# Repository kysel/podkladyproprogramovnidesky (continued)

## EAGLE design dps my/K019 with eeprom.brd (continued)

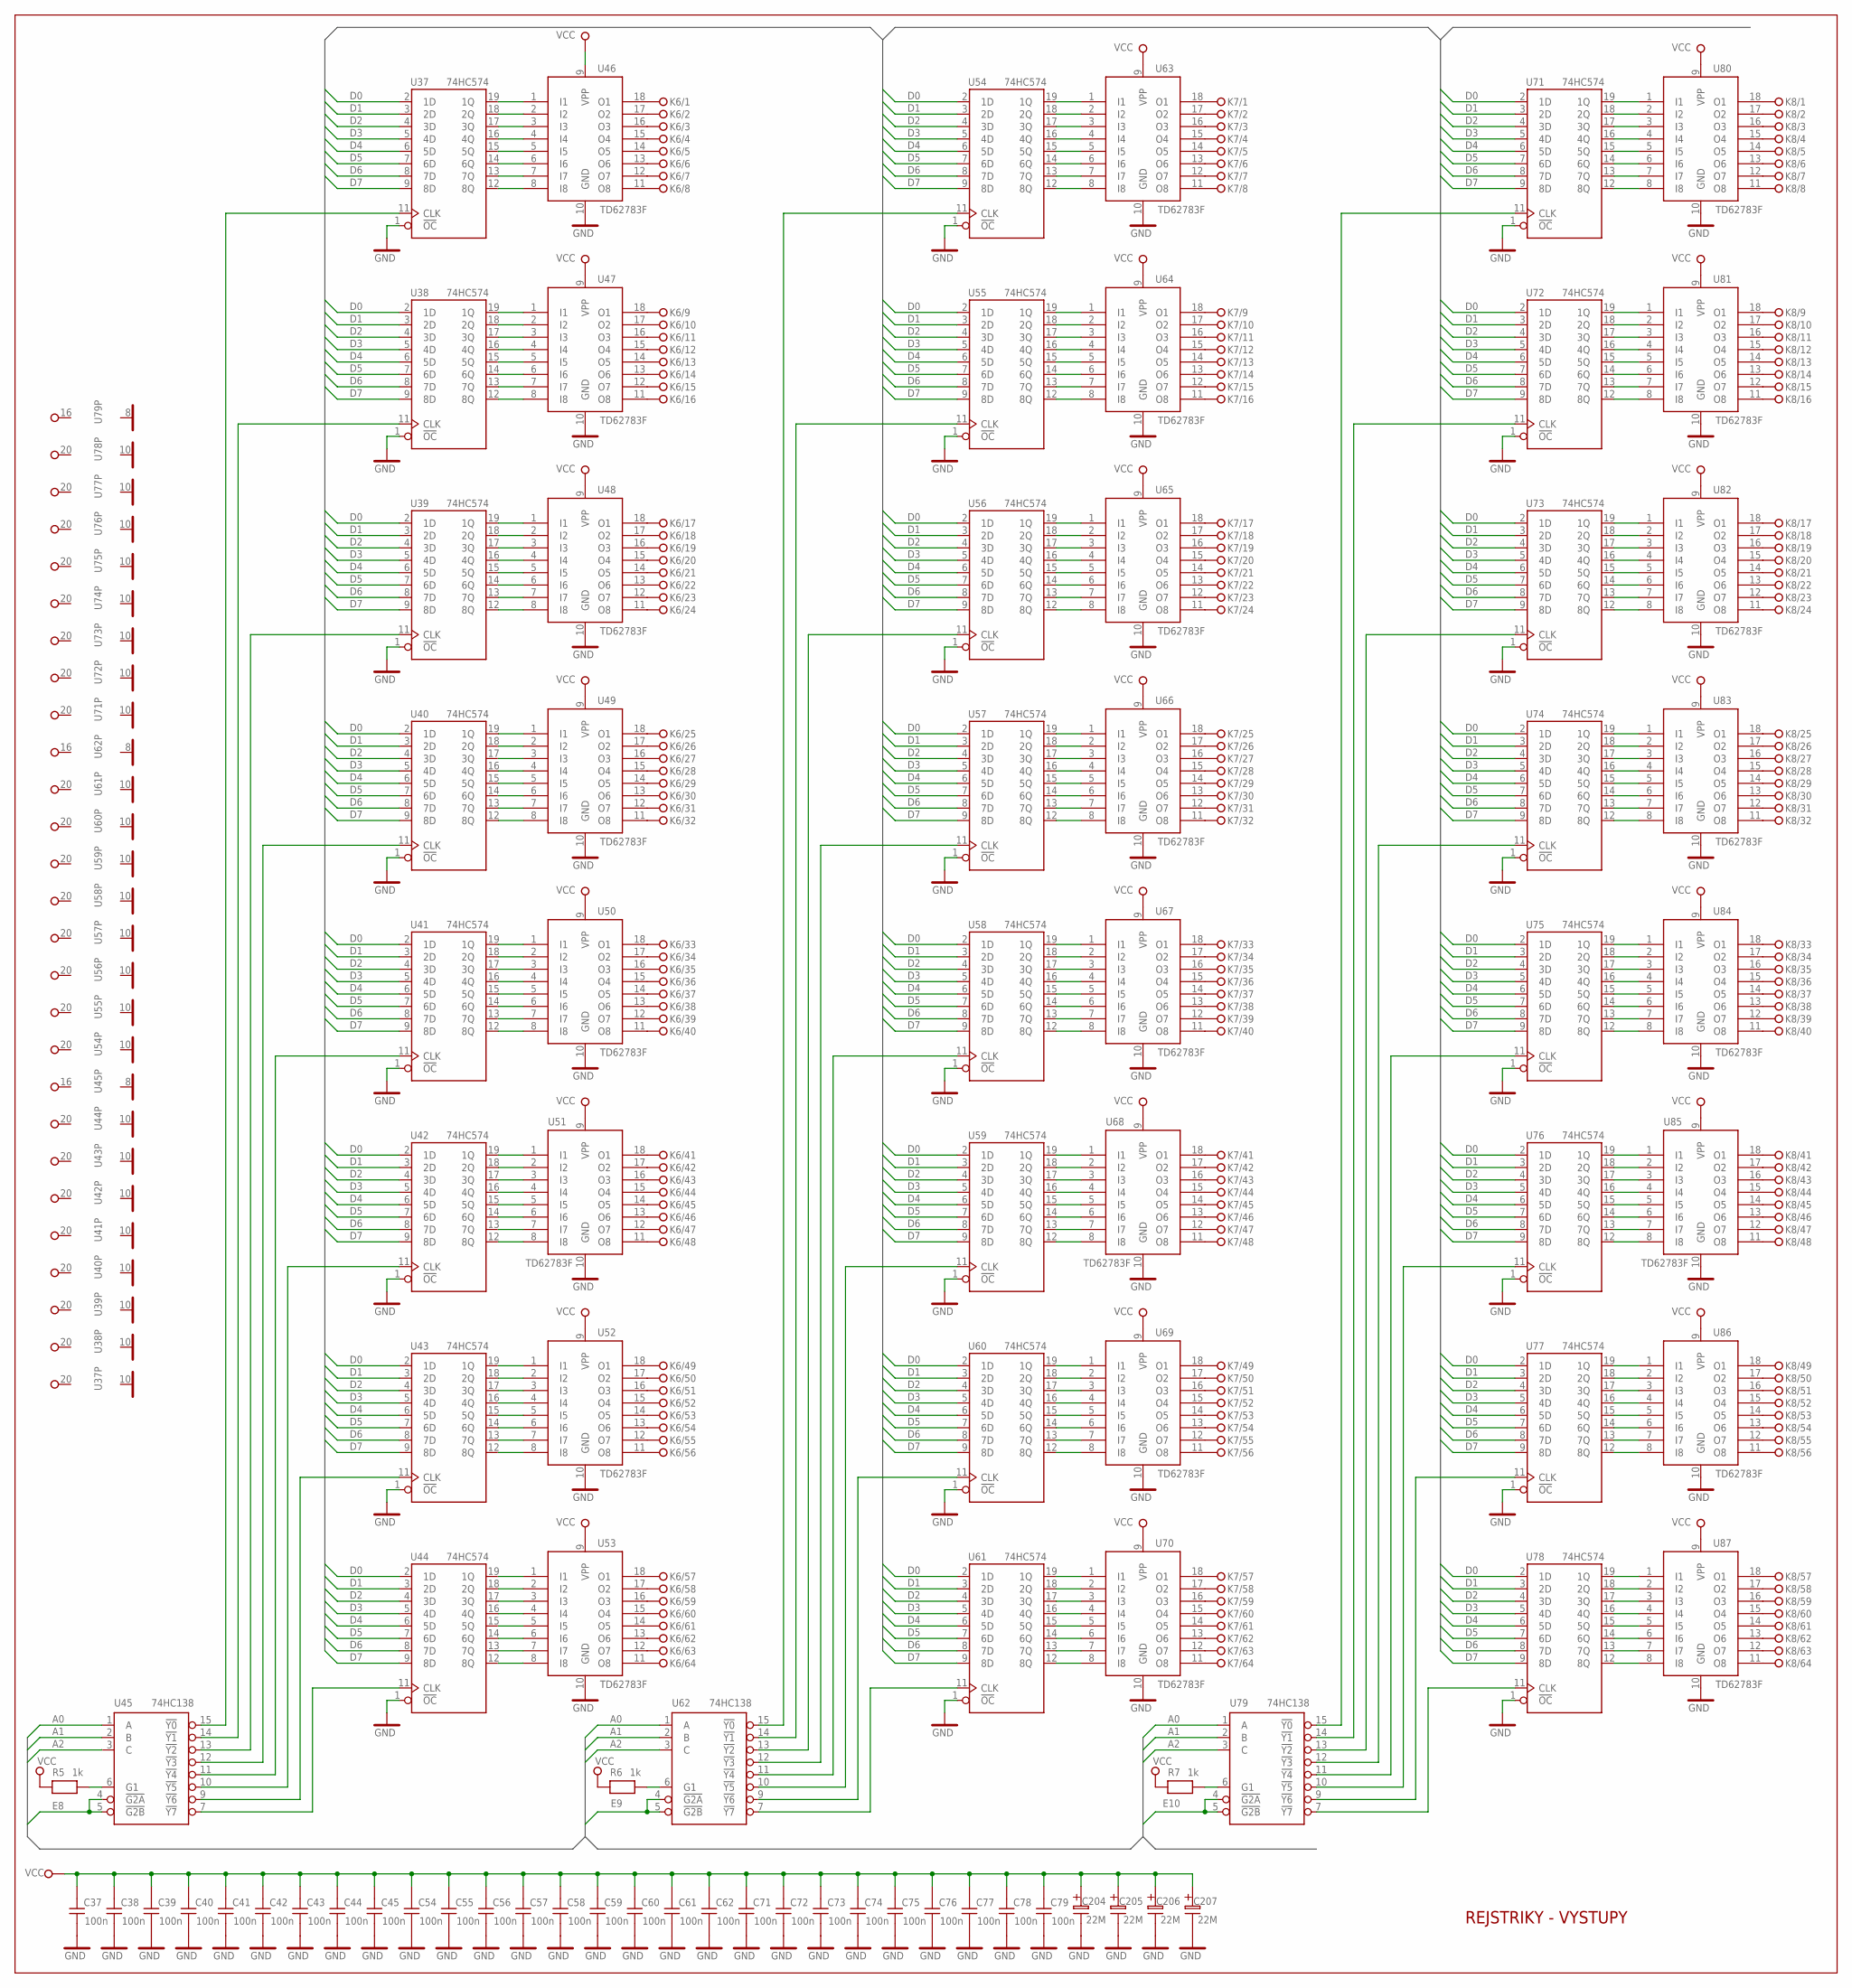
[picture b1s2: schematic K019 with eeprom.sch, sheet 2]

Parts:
C37, C38, C39, C40, C41, C42, C43, C44, C45, C54, C55, C56, C57, C58, C59, C60, C61, C62, C71, C72, C73, C74, C75, C76, C77, C78, C79: 100n; C-5-2X8
C204, C205, C206, C207: 22M; EC-2/5
K6, K7, K8: KON64
R5, R6, R7: 1k; R-7,5
U37, U38, U39, U40, U41, U42, U43, U44, U54, U55, U56, U57, U58, U59, U60, U61, U71, U72, U73, U74, U75, U76, U77, U78: 74HC574; DIL20
U45, U62, U79: 74HC138; DIL16
U46, U47, U48, U49, U50, U51, U52, U53, U63, U64, U65, U66, U67, U68, U69, U70, U80, U81, U82, U83, U84, U85, U86, U87: TD62783F; DIL18

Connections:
A0: U45.1 (A), U62.1 (A), U79.1 (A); also elsewhere on the board
A1: U45.2 (B), U62.2 (B), U79.2 (B); also elsewhere on the board
A2: U45.3 (C), U62.3 (C), U79.3 (C); also elsewhere on the board
D0: U37.2 (1D), U38.2 (1D), U39.2 (1D), U40.2 (1D), U41.2 (1D), U42.2 (1D), U43.2 (1D), U44.2 (1D), U54.2 (1D), U55.2 (1D), U56.2 (1D), U57.2 (1D), U58.2 (1D), U59.2 (1D), U60.2 (1D), U61.2 (1D), U71.2 (1D), U72.2 (1D), U73.2 (1D), U74.2 (1D), U75.2 (1D), U76.2 (1D), U77.2 (1D), U78.2 (1D); also elsewhere on the board
D1: U37.3 (2D), U38.3 (2D), U39.3 (2D), U40.3 (2D), U41.3 (2D), U42.3 (2D), U43.3 (2D), U44.3 (2D), U54.3 (2D), U55.3 (2D), U56.3 (2D), U57.3 (2D), U58.3 (2D), U59.3 (2D), U60.3 (2D), U61.3 (2D), U71.3 (2D), U72.3 (2D), U73.3 (2D), U74.3 (2D), U75.3 (2D), U76.3 (2D), U77.3 (2D), U78.3 (2D); also elsewhere on the board
D2: U37.4 (3D), U38.4 (3D), U39.4 (3D), U40.4 (3D), U41.4 (3D), U42.4 (3D), U43.4 (3D), U44.4 (3D), U54.4 (3D), U55.4 (3D), U56.4 (3D), U57.4 (3D), U58.4 (3D), U59.4 (3D), U60.4 (3D), U61.4 (3D), U71.4 (3D), U72.4 (3D), U73.4 (3D), U74.4 (3D), U75.4 (3D), U76.4 (3D), U77.4 (3D), U78.4 (3D); also elsewhere on the board
D3: U37.5 (4D), U38.5 (4D), U39.5 (4D), U40.5 (4D), U41.5 (4D), U42.5 (4D), U43.5 (4D), U44.5 (4D), U54.5 (4D), U55.5 (4D), U56.5 (4D), U57.5 (4D), U58.5 (4D), U59.5 (4D), U60.5 (4D), U61.5 (4D), U71.5 (4D), U72.5 (4D), U73.5 (4D), U74.5 (4D), U75.5 (4D), U76.5 (4D), U77.5 (4D), U78.5 (4D); also elsewhere on the board
D4: U37.6 (5D), U38.6 (5D), U39.6 (5D), U40.6 (5D), U41.6 (5D), U42.6 (5D), U43.6 (5D), U44.6 (5D), U54.6 (5D), U55.6 (5D), U56.6 (5D), U57.6 (5D), U58.6 (5D), U59.6 (5D), U60.6 (5D), U61.6 (5D), U71.6 (5D), U72.6 (5D), U73.6 (5D), U74.6 (5D), U75.6 (5D), U76.6 (5D), U77.6 (5D), U78.6 (5D); also elsewhere on the board
D5: U37.7 (6D), U38.7 (6D), U39.7 (6D), U40.7 (6D), U41.7 (6D), U42.7 (6D), U43.7 (6D), U44.7 (6D), U54.7 (6D), U55.7 (6D), U56.7 (6D), U57.7 (6D), U58.7 (6D), U59.7 (6D), U60.7 (6D), U61.7 (6D), U71.7 (6D), U72.7 (6D), U73.7 (6D), U74.7 (6D), U75.7 (6D), U76.7 (6D), U77.7 (6D), U78.7 (6D); also elsewhere on the board
D6: U37.8 (7D), U38.8 (7D), U39.8 (7D), U40.8 (7D), U41.8 (7D), U42.8 (7D), U43.8 (7D), U44.8 (7D), U54.8 (7D), U55.8 (7D), U56.8 (7D), U57.8 (7D), U58.8 (7D), U59.8 (7D), U60.8 (7D), U61.8 (7D), U71.8 (7D), U72.8 (7D), U73.8 (7D), U74.8 (7D), U75.8 (7D), U76.8 (7D), U77.8 (7D), U78.8 (7D); also elsewhere on the board
D7: U37.9 (8D), U38.9 (8D), U39.9 (8D), U40.9 (8D), U41.9 (8D), U42.9 (8D), U43.9 (8D), U44.9 (8D), U54.9 (8D), U55.9 (8D), U56.9 (8D), U57.9 (8D), U58.9 (8D), U59.9 (8D), U60.9 (8D), U61.9 (8D), U71.9 (8D), U72.9 (8D), U73.9 (8D), U74.9 (8D), U75.9 (8D), U76.9 (8D), U77.9 (8D), U78.9 (8D); also elsewhere on the board
E8: U45.4 (!G2A), U45.5 (!G2B); also elsewhere on the board
E9: U62.4 (!G2A), U62.5 (!G2B); also elsewhere on the board
E10: U79.4 (!G2A), U79.5 (!G2B); also elsewhere on the board
GND: C37.1, C38.1, C39.1, C40.1, C41.1, C42.1, C43.1, C44.1, C45.1, C54.1, C55.1, C56.1, C57.1, C58.1, C59.1, C60.1, C61.1, C62.1, C71.1, C72.1, C73.1, C74.1, C75.1, C76.1, C77.1, C78.1, C79.1, C204.1, C205.1, C206.1, C207.1, U37.1 (!OC), U37.10 (GND), U38.1 (!OC), U38.10 (GND), U39.1 (!OC), U39.10 (GND), U40.1 (!OC), U40.10 (GND), U41.1 (!OC), U41.10 (GND), U42.1 (!OC), U42.10 (GND), U43.1 (!OC), U43.10 (GND), U44.1 (!OC), U44.10 (GND), U45.8 (GND), U46.10 (GND), U47.10 (GND), U48.10 (GND), U49.10 (GND), U50.10 (GND), U51.10 (GND), U52.10 (GND), U53.10 (GND), U54.1 (!OC), U54.10 (GND), U55.1 (!OC), U55.10 (GND), U56.1 (!OC), U56.10 (GND), U57.1 (!OC), U57.10 (GND), U58.1 (!OC), U58.10 (GND), U59.1 (!OC), U59.10 (GND), U60.1 (!OC), U60.10 (GND), U61.1 (!OC), U61.10 (GND), U62.8 (GND), U63.10 (GND), U64.10 (GND), U65.10 (GND), U66.10 (GND), U67.10 (GND), U68.10 (GND), U69.10 (GND), U70.10 (GND), U71.1 (!OC), U71.10 (GND), U72.1 (!OC), U72.10 (GND), U73.1 (!OC), U73.10 (GND), U74.1 (!OC), U74.10 (GND), U75.1 (!OC), U75.10 (GND), U76.1 (!OC), U76.10 (GND), U77.1 (!OC), U77.10 (GND), U78.1 (!OC), U78.10 (GND), U79.8 (GND), U80.10 (GND), U81.10 (GND), U82.10 (GND), U83.10 (GND), U84.10 (GND), U85.10 (GND), U86.10 (GND), U87.10 (GND); also elsewhere on the board
unnamed: K6.1, U46.18 (O1)
unnamed: K6.2, U46.17 (O2)
unnamed: K6.3, U46.16 (O3)
unnamed: K6.4, U46.15 (O4)
unnamed: K6.5, U46.14 (O5)
unnamed: K6.6, U46.13 (O6)
unnamed: K6.7, U46.12 (O7)
unnamed: K6.8, U46.11 (O8)
unnamed: K6.9, U47.18 (O1)
unnamed: K6.10, U47.17 (O2)
unnamed: K6.11, U47.16 (O3)
unnamed: K6.12, U47.15 (O4)
unnamed: K6.13, U47.14 (O5)
unnamed: K6.14, U47.13 (O6)
unnamed: K6.15, U47.12 (O7)
unnamed: K6.16, U47.11 (O8)
unnamed: K6.17, U48.18 (O1)
unnamed: K6.18, U48.17 (O2)
unnamed: K6.19, U48.16 (O3)
unnamed: K6.20, U48.15 (O4)
unnamed: K6.21, U48.14 (O5)
unnamed: K6.22, U48.13 (O6)
unnamed: K6.23, U48.12 (O7)
unnamed: K6.24, U48.11 (O8)
unnamed: K6.25, U49.18 (O1)
unnamed: K6.26, U49.17 (O2)
unnamed: K6.27, U49.16 (O3)
unnamed: K6.28, U49.15 (O4)
unnamed: K6.29, U49.14 (O5)
unnamed: K6.30, U49.13 (O6)
unnamed: K6.31, U49.12 (O7)
unnamed: K6.32, U49.11 (O8)
unnamed: K6.33, U50.18 (O1)
unnamed: K6.34, U50.17 (O2)
unnamed: K6.35, U50.16 (O3)
unnamed: K6.36, U50.15 (O4)
unnamed: K6.37, U50.14 (O5)
unnamed: K6.38, U50.13 (O6)
unnamed: K6.39, U50.12 (O7)
unnamed: K6.40, U50.11 (O8)
unnamed: K6.41, U51.18 (O1)
unnamed: K6.42, U51.17 (O2)
unnamed: K6.43, U51.16 (O3)
unnamed: K6.44, U51.15 (O4)
unnamed: K6.45, U51.14 (O5)
unnamed: K6.46, U51.13 (O6)
unnamed: K6.47, U51.12 (O7)
unnamed: K6.48, U51.11 (O8)
unnamed: K6.49, U52.18 (O1)
unnamed: K6.50, U52.17 (O2)
unnamed: K6.51, U52.16 (O3)
unnamed: K6.52, U52.15 (O4)
unnamed: K6.53, U52.14 (O5)
unnamed: K6.54, U52.13 (O6)
unnamed: K6.55, U52.12 (O7)
unnamed: K6.56, U52.11 (O8)
unnamed: K6.57, U53.18 (O1)
unnamed: K6.58, U53.17 (O2)
unnamed: K6.59, U53.16 (O3)
unnamed: K6.60, U53.15 (O4)
unnamed: K6.61, U53.14 (O5)
unnamed: K6.62, U53.13 (O6)
unnamed: K6.63, U53.12 (O7)
unnamed: K6.64, U53.11 (O8)
unnamed: U44.12 (8Q), U53.8 (I8)
unnamed: U44.13 (7Q), U53.7 (I7)
unnamed: U44.14 (6Q), U53.6 (I6)
unnamed: U44.15 (5Q), U53.5 (I5)
unnamed: U44.16 (4Q), U53.4 (I4)
unnamed: U44.17 (3Q), U53.3 (I3)
unnamed: U44.18 (2Q), U53.2 (I2)
unnamed: U44.19 (1Q), U53.1 (I1)
unnamed: U43.12 (8Q), U52.8 (I8)
unnamed: U43.13 (7Q), U52.7 (I7)
unnamed: U43.14 (6Q), U52.6 (I6)
unnamed: U43.15 (5Q), U52.5 (I5)
unnamed: U43.16 (4Q), U52.4 (I4)
unnamed: U43.17 (3Q), U52.3 (I3)
unnamed: U43.18 (2Q), U52.2 (I2)
unnamed: U43.19 (1Q), U52.1 (I1)
unnamed: U41.19 (1Q), U50.1 (I1)
unnamed: U41.18 (2Q), U50.2 (I2)
unnamed: U41.17 (3Q), U50.3 (I3)
unnamed: U41.16 (4Q), U50.4 (I4)
unnamed: U41.15 (5Q), U50.5 (I5)
unnamed: U41.14 (6Q), U50.6 (I6)
unnamed: U41.13 (7Q), U50.7 (I7)
unnamed: U41.12 (8Q), U50.8 (I8)
unnamed: U42.12 (8Q), U51.8 (I8)
unnamed: U42.13 (7Q), U51.7 (I7)
unnamed: U42.14 (6Q), U51.6 (I6)
unnamed: U42.15 (5Q), U51.5 (I5)
unnamed: U42.16 (4Q), U51.4 (I4)
unnamed: U42.17 (3Q), U51.3 (I3)
unnamed: U42.18 (2Q), U51.2 (I2)
unnamed: U40.12 (8Q), U49.8 (I8)
unnamed: U40.13 (7Q), U49.7 (I7)
unnamed: U40.14 (6Q), U49.6 (I6)
unnamed: U40.15 (5Q), U49.5 (I5)
unnamed: U40.16 (4Q), U49.4 (I4)
unnamed: U40.17 (3Q), U49.3 (I3)
unnamed: U40.18 (2Q), U49.2 (I2)
unnamed: U40.19 (1Q), U49.1 (I1)
unnamed: U38.19 (1Q), U47.1 (I1)
unnamed: U38.18 (2Q), U47.2 (I2)
unnamed: U38.17 (3Q), U47.3 (I3)
unnamed: U38.16 (4Q), U47.4 (I4)
unnamed: U38.15 (5Q), U47.5 (I5)
unnamed: U38.14 (6Q), U47.6 (I6)
unnamed: U38.13 (7Q), U47.7 (I7)
unnamed: U38.12 (8Q), U47.8 (I8)
unnamed: U39.19 (1Q), U48.1 (I1)
unnamed: U39.18 (2Q), U48.2 (I2)
unnamed: U39.17 (3Q), U48.3 (I3)
unnamed: U39.16 (4Q), U48.4 (I4)
unnamed: U39.15 (5Q), U48.5 (I5)
unnamed: U39.14 (6Q), U48.6 (I6)
unnamed: U39.13 (7Q), U48.7 (I7)
unnamed: U39.12 (8Q), U48.8 (I8)
unnamed: U37.12 (8Q), U46.8 (I8)
unnamed: U37.13 (7Q), U46.7 (I7)
unnamed: U37.14 (6Q), U46.6 (I6)
unnamed: U37.15 (5Q), U46.5 (I5)
unnamed: U37.16 (4Q), U46.4 (I4)
unnamed: U37.17 (3Q), U46.3 (I3)
unnamed: U37.18 (2Q), U46.2 (I2)
unnamed: U37.19 (1Q), U46.1 (I1)
unnamed: U42.19 (1Q), U51.1 (I1)
unnamed: U44.11 (CLK), U45.7 (!Y7)
unnamed: U43.11 (CLK), U45.9 (!Y6)
unnamed: U42.11 (CLK), U45.10 (!Y5)
unnamed: U41.11 (CLK), U45.11 (!Y4)
unnamed: U40.11 (CLK), U45.12 (!Y3)
unnamed: U39.11 (CLK), U45.13 (!Y2)
unnamed: U38.11 (CLK), U45.14 (!Y1)
unnamed: U37.11 (CLK), U45.15 (!Y0)
unnamed: R5.2, U45.6 (G1)
unnamed: K7.1, U63.18 (O1)
unnamed: K7.2, U63.17 (O2)
unnamed: K7.3, U63.16 (O3)
unnamed: K7.4, U63.15 (O4)
unnamed: K7.5, U63.14 (O5)
unnamed: K7.6, U63.13 (O6)
unnamed: K7.7, U63.12 (O7)
unnamed: K7.8, U63.11 (O8)
unnamed: K7.9, U64.18 (O1)
unnamed: K7.10, U64.17 (O2)
unnamed: K7.11, U64.16 (O3)
unnamed: K7.12, U64.15 (O4)
unnamed: K7.13, U64.14 (O5)
unnamed: K7.14, U64.13 (O6)
unnamed: K7.15, U64.12 (O7)
unnamed: K7.16, U64.11 (O8)
unnamed: K7.25, U66.18 (O1)
unnamed: K7.26, U66.17 (O2)
unnamed: K7.27, U66.16 (O3)
unnamed: K7.28, U66.15 (O4)
unnamed: K7.29, U66.14 (O5)
unnamed: K7.30, U66.13 (O6)
unnamed: K7.31, U66.12 (O7)
unnamed: K7.32, U66.11 (O8)
unnamed: K7.33, U67.18 (O1)
unnamed: K7.34, U67.17 (O2)
unnamed: K7.35, U67.16 (O3)
unnamed: K7.36, U67.15 (O4)
unnamed: K7.37, U67.14 (O5)
unnamed: K7.38, U67.13 (O6)
unnamed: K7.39, U67.12 (O7)
unnamed: K7.40, U67.11 (O8)
unnamed: K7.41, U68.18 (O1)
unnamed: K7.42, U68.17 (O2)
unnamed: K7.43, U68.16 (O3)
unnamed: K7.44, U68.15 (O4)
unnamed: K7.45, U68.14 (O5)
unnamed: K7.46, U68.13 (O6)
unnamed: K7.47, U68.12 (O7)
unnamed: K7.48, U68.11 (O8)
unnamed: K7.49, U69.18 (O1)
unnamed: K7.50, U69.17 (O2)
unnamed: K7.51, U69.16 (O3)
unnamed: K7.52, U69.15 (O4)
unnamed: K7.53, U69.14 (O5)
unnamed: K7.54, U69.13 (O6)
unnamed: K7.55, U69.12 (O7)
unnamed: K7.56, U69.11 (O8)
unnamed: K7.57, U70.18 (O1)
unnamed: K7.58, U70.17 (O2)
unnamed: K7.59, U70.16 (O3)
unnamed: K7.60, U70.15 (O4)
unnamed: K7.61, U70.14 (O5)
unnamed: K7.62, U70.13 (O6)
unnamed: K7.63, U70.12 (O7)
unnamed: K7.64, U70.11 (O8)
unnamed: U61.12 (8Q), U70.8 (I8)
unnamed: U61.13 (7Q), U70.7 (I7)
unnamed: U61.14 (6Q), U70.6 (I6)
unnamed: U61.15 (5Q), U70.5 (I5)
unnamed: U61.16 (4Q), U70.4 (I4)
unnamed: U61.17 (3Q), U70.3 (I3)
unnamed: U61.18 (2Q), U70.2 (I2)
unnamed: U61.19 (1Q), U70.1 (I1)
unnamed: U60.12 (8Q), U69.8 (I8)
unnamed: U60.13 (7Q), U69.7 (I7)
unnamed: U60.14 (6Q), U69.6 (I6)
unnamed: U60.15 (5Q), U69.5 (I5)
unnamed: U60.16 (4Q), U69.4 (I4)
unnamed: U60.17 (3Q), U69.3 (I3)
unnamed: U60.18 (2Q), U69.2 (I2)
unnamed: U60.19 (1Q), U69.1 (I1)
unnamed: U58.19 (1Q), U67.1 (I1)
unnamed: U58.18 (2Q), U67.2 (I2)
unnamed: U58.17 (3Q), U67.3 (I3)
unnamed: U58.16 (4Q), U67.4 (I4)
unnamed: U58.15 (5Q), U67.5 (I5)
unnamed: U58.14 (6Q), U67.6 (I6)
unnamed: U58.13 (7Q), U67.7 (I7)
unnamed: U58.12 (8Q), U67.8 (I8)
unnamed: U59.19 (1Q), U68.1 (I1)
unnamed: U59.18 (2Q), U68.2 (I2)
unnamed: U59.17 (3Q), U68.3 (I3)
unnamed: U59.16 (4Q), U68.4 (I4)
unnamed: U59.15 (5Q), U68.5 (I5)
unnamed: U59.14 (6Q), U68.6 (I6)
unnamed: U59.13 (7Q), U68.7 (I7)
unnamed: K7.17, U65.18 (O1)
unnamed: K7.18, U65.17 (O2)
unnamed: K7.19, U65.16 (O3)
unnamed: K7.20, U65.15 (O4)
unnamed: K7.21, U65.14 (O5)
unnamed: K7.22, U65.13 (O6)
unnamed: K7.23, U65.12 (O7)
unnamed: K7.24, U65.11 (O8)
unnamed: U57.12 (8Q), U66.8 (I8)
unnamed: U57.13 (7Q), U66.7 (I7)
unnamed: U57.14 (6Q), U66.6 (I6)
unnamed: U57.15 (5Q), U66.5 (I5)
unnamed: U57.16 (4Q), U66.4 (I4)
unnamed: U57.17 (3Q), U66.3 (I3)
unnamed: U57.18 (2Q), U66.2 (I2)
unnamed: U57.19 (1Q), U66.1 (I1)
unnamed: U55.19 (1Q), U64.1 (I1)
unnamed: U55.18 (2Q), U64.2 (I2)
unnamed: U55.17 (3Q), U64.3 (I3)
unnamed: U55.16 (4Q), U64.4 (I4)
unnamed: U55.15 (5Q), U64.5 (I5)
unnamed: U55.14 (6Q), U64.6 (I6)
unnamed: U55.13 (7Q), U64.7 (I7)
unnamed: U55.12 (8Q), U64.8 (I8)
unnamed: U56.19 (1Q), U65.1 (I1)
unnamed: U56.18 (2Q), U65.2 (I2)
unnamed: U56.17 (3Q), U65.3 (I3)
unnamed: U56.16 (4Q), U65.4 (I4)
unnamed: U56.15 (5Q), U65.5 (I5)
unnamed: U56.14 (6Q), U65.6 (I6)
unnamed: U56.13 (7Q), U65.7 (I7)
unnamed: U56.12 (8Q), U65.8 (I8)
unnamed: U54.12 (8Q), U63.8 (I8)
unnamed: U54.13 (7Q), U63.7 (I7)
unnamed: U54.14 (6Q), U63.6 (I6)
unnamed: U54.15 (5Q), U63.5 (I5)
unnamed: U54.16 (4Q), U63.4 (I4)
unnamed: U54.17 (3Q), U63.3 (I3)
unnamed: U54.18 (2Q), U63.2 (I2)
unnamed: U54.19 (1Q), U63.1 (I1)
unnamed: U59.12 (8Q), U68.8 (I8)
unnamed: U60.11 (CLK), U62.9 (!Y6)
unnamed: U59.11 (CLK), U62.10 (!Y5)
unnamed: U58.11 (CLK), U62.11 (!Y4)
unnamed: U57.11 (CLK), U62.12 (!Y3)
unnamed: U56.11 (CLK), U62.13 (!Y2)
unnamed: U55.11 (CLK), U62.14 (!Y1)
unnamed: U54.11 (CLK), U62.15 (!Y0)
unnamed: U61.11 (CLK), U62.7 (!Y7)
unnamed: R6.2, U62.6 (G1)
unnamed: K8.1, U80.18 (O1)
unnamed: K8.2, U80.17 (O2)
unnamed: K8.3, U80.16 (O3)
unnamed: K8.4, U80.15 (O4)
unnamed: K8.5, U80.14 (O5)
unnamed: K8.6, U80.13 (O6)
unnamed: K8.7, U80.12 (O7)
unnamed: K8.8, U80.11 (O8)
unnamed: K8.9, U81.18 (O1)
unnamed: K8.10, U81.17 (O2)
unnamed: K8.11, U81.16 (O3)
unnamed: K8.12, U81.15 (O4)
unnamed: K8.13, U81.14 (O5)
unnamed: K8.14, U81.13 (O6)
unnamed: K8.15, U81.12 (O7)
unnamed: K8.16, U81.11 (O8)
unnamed: K8.25, U83.18 (O1)
unnamed: K8.26, U83.17 (O2)
unnamed: K8.27, U83.16 (O3)
unnamed: K8.28, U83.15 (O4)
unnamed: K8.29, U83.14 (O5)
unnamed: K8.30, U83.13 (O6)
unnamed: K8.31, U83.12 (O7)
unnamed: K8.32, U83.11 (O8)
unnamed: K8.33, U84.18 (O1)
unnamed: K8.34, U84.17 (O2)
unnamed: K8.35, U84.16 (O3)
unnamed: K8.36, U84.15 (O4)
unnamed: K8.37, U84.14 (O5)
unnamed: K8.38, U84.13 (O6)
unnamed: K8.39, U84.12 (O7)
unnamed: K8.40, U84.11 (O8)
unnamed: K8.41, U85.18 (O1)
unnamed: K8.42, U85.17 (O2)
unnamed: K8.43, U85.16 (O3)
unnamed: K8.44, U85.15 (O4)
unnamed: K8.45, U85.14 (O5)
unnamed: K8.46, U85.13 (O6)
unnamed: K8.47, U85.12 (O7)
unnamed: K8.48, U85.11 (O8)
unnamed: K8.49, U86.18 (O1)
unnamed: K8.50, U86.17 (O2)
unnamed: K8.51, U86.16 (O3)
unnamed: K8.52, U86.15 (O4)
unnamed: K8.53, U86.14 (O5)
unnamed: K8.54, U86.13 (O6)
unnamed: K8.55, U86.12 (O7)
unnamed: K8.56, U86.11 (O8)
unnamed: K8.57, U87.18 (O1)
unnamed: K8.58, U87.17 (O2)
unnamed: K8.59, U87.16 (O3)
unnamed: K8.60, U87.15 (O4)
unnamed: K8.61, U87.14 (O5)
unnamed: K8.62, U87.13 (O6)
unnamed: K8.63, U87.12 (O7)
unnamed: K8.64, U87.11 (O8)
unnamed: U78.12 (8Q), U87.8 (I8)
unnamed: U78.13 (7Q), U87.7 (I7)
unnamed: U78.14 (6Q), U87.6 (I6)
unnamed: U78.15 (5Q), U87.5 (I5)
unnamed: U78.16 (4Q), U87.4 (I4)
unnamed: U78.17 (3Q), U87.3 (I3)
unnamed: U78.18 (2Q), U87.2 (I2)
unnamed: U78.19 (1Q), U87.1 (I1)
unnamed: U77.12 (8Q), U86.8 (I8)
unnamed: U77.13 (7Q), U86.7 (I7)
unnamed: U77.14 (6Q), U86.6 (I6)
unnamed: U77.15 (5Q), U86.5 (I5)
unnamed: U77.16 (4Q), U86.4 (I4)
unnamed: U77.17 (3Q), U86.3 (I3)
unnamed: U77.18 (2Q), U86.2 (I2)
unnamed: U77.19 (1Q), U86.1 (I1)
unnamed: U75.19 (1Q), U84.1 (I1)
unnamed: U75.18 (2Q), U84.2 (I2)
unnamed: U75.17 (3Q), U84.3 (I3)
unnamed: U75.16 (4Q), U84.4 (I4)
unnamed: U75.15 (5Q), U84.5 (I5)
unnamed: U75.14 (6Q), U84.6 (I6)
unnamed: U75.13 (7Q), U84.7 (I7)
unnamed: U75.12 (8Q), U84.8 (I8)
unnamed: U76.12 (8Q), U85.8 (I8)
unnamed: U76.13 (7Q), U85.7 (I7)
unnamed: U76.14 (6Q), U85.6 (I6)
unnamed: U76.15 (5Q), U85.5 (I5)
unnamed: U76.16 (4Q), U85.4 (I4)
unnamed: U76.17 (3Q), U85.3 (I3)
unnamed: U76.18 (2Q), U85.2 (I2)
unnamed: K8.17, U82.18 (O1)
unnamed: K8.18, U82.17 (O2)
unnamed: K8.19, U82.16 (O3)
unnamed: K8.20, U82.15 (O4)
unnamed: K8.21, U82.14 (O5)
unnamed: K8.22, U82.13 (O6)
unnamed: K8.23, U82.12 (O7)
unnamed: K8.24, U82.11 (O8)
unnamed: U74.12 (8Q), U83.8 (I8)
unnamed: U74.13 (7Q), U83.7 (I7)
unnamed: U74.14 (6Q), U83.6 (I6)
unnamed: U74.15 (5Q), U83.5 (I5)
unnamed: U74.16 (4Q), U83.4 (I4)
unnamed: U74.17 (3Q), U83.3 (I3)
unnamed: U74.18 (2Q), U83.2 (I2)
unnamed: U74.19 (1Q), U83.1 (I1)
unnamed: U72.19 (1Q), U81.1 (I1)
unnamed: U72.18 (2Q), U81.2 (I2)
unnamed: U72.17 (3Q), U81.3 (I3)
unnamed: U72.16 (4Q), U81.4 (I4)
unnamed: U72.15 (5Q), U81.5 (I5)
unnamed: U72.14 (6Q), U81.6 (I6)
unnamed: U72.13 (7Q), U81.7 (I7)
unnamed: U72.12 (8Q), U81.8 (I8)
unnamed: U73.19 (1Q), U82.1 (I1)
unnamed: U73.18 (2Q), U82.2 (I2)
unnamed: U73.17 (3Q), U82.3 (I3)
unnamed: U73.16 (4Q), U82.4 (I4)
unnamed: U73.15 (5Q), U82.5 (I5)
unnamed: U73.14 (6Q), U82.6 (I6)
unnamed: U73.13 (7Q), U82.7 (I7)
unnamed: U73.12 (8Q), U82.8 (I8)
unnamed: U71.12 (8Q), U80.8 (I8)
unnamed: U71.13 (7Q), U80.7 (I7)
unnamed: U71.14 (6Q), U80.6 (I6)
unnamed: U71.15 (5Q), U80.5 (I5)
unnamed: U71.16 (4Q), U80.4 (I4)
unnamed: U71.17 (3Q), U80.3 (I3)
unnamed: U71.18 (2Q), U80.2 (I2)
unnamed: U71.19 (1Q), U80.1 (I1)
unnamed: U76.19 (1Q), U85.1 (I1)
unnamed: U77.11 (CLK), U79.9 (!Y6)
unnamed: U76.11 (CLK), U79.10 (!Y5)
unnamed: U75.11 (CLK), U79.11 (!Y4)
unnamed: U74.11 (CLK), U79.12 (!Y3)
unnamed: U73.11 (CLK), U79.13 (!Y2)
unnamed: U72.11 (CLK), U79.14 (!Y1)
unnamed: U71.11 (CLK), U79.15 (!Y0)
unnamed: U78.11 (CLK), U79.7 (!Y7)
unnamed: R7.2, U79.6 (G1)
VCC: C37.2, C38.2, C39.2, C40.2, C41.2, C42.2, C43.2, C44.2, C45.2, C54.2, C55.2, C56.2, C57.2, C58.2, C59.2, C60.2, C61.2, C62.2, C71.2, C72.2, C73.2, C74.2, C75.2, C76.2, C77.2, C78.2, C79.2, C204.2, C205.2, C206.2, C207.2, R5.1, R6.1, R7.1, U37.20 (VCC), U38.20 (VCC), U39.20 (VCC), U40.20 (VCC), U41.20 (VCC), U42.20 (VCC), U43.20 (VCC), U44.20 (VCC), U45.16 (VCC), U46.9 (VPP), U47.9 (VPP), U48.9 (VPP), U49.9 (VPP), U50.9 (VPP), U51.9 (VPP), U52.9 (VPP), U53.9 (VPP), U54.20 (VCC), U55.20 (VCC), U56.20 (VCC), U57.20 (VCC), U58.20 (VCC), U59.20 (VCC), U60.20 (VCC), U61.20 (VCC), U62.16 (VCC), U63.9 (VPP), U64.9 (VPP), U65.9 (VPP), U66.9 (VPP), U67.9 (VPP), U68.9 (VPP), U69.9 (VPP), U70.9 (VPP), U71.20 (VCC), U72.20 (VCC), U73.20 (VCC), U74.20 (VCC), U75.20 (VCC), U76.20 (VCC), U77.20 (VCC), U78.20 (VCC), U79.16 (VCC), U80.9 (VPP), U81.9 (VPP), U82.9 (VPP), U83.9 (VPP), U84.9 (VPP), U85.9 (VPP), U86.9 (VPP), U87.9 (VPP); also elsewhere on the board

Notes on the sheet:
REJSTRIKY - VYSTUPY
